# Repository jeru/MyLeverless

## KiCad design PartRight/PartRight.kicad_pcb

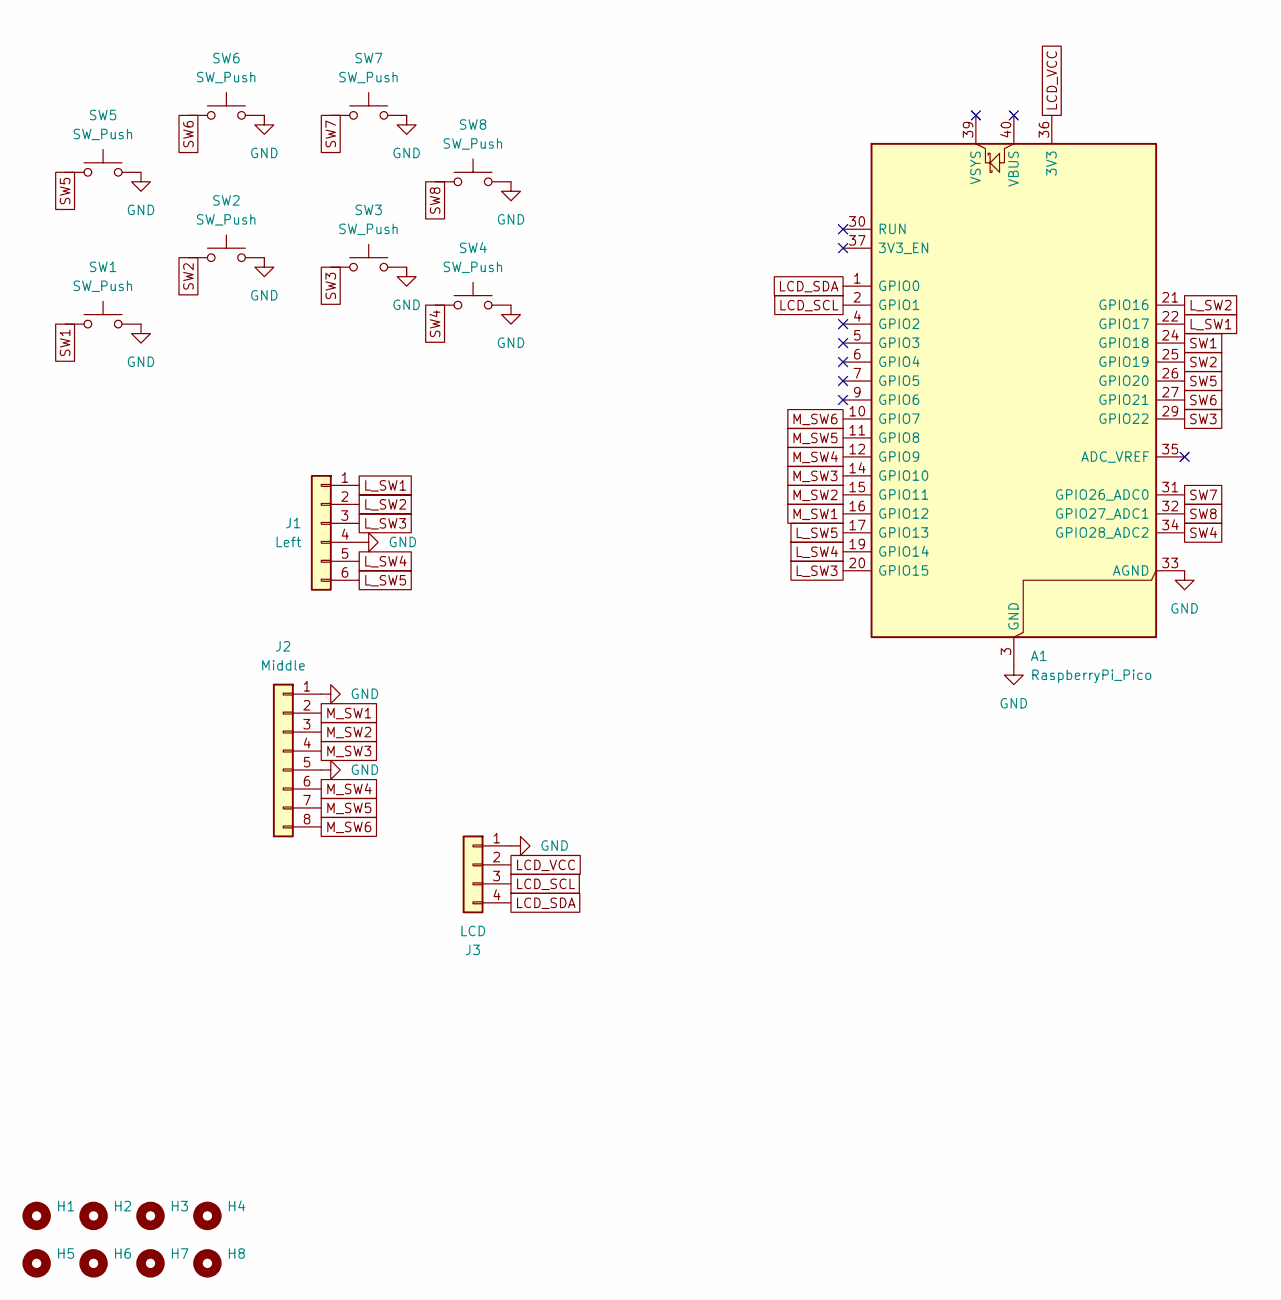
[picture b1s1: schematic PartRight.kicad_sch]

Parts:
A1: RaspberryPi_Pico; RaspberryPi_Pico_Common_SMD
H1, H2, H3, H4, H5, H6, H7, H8: MountingHole; MountingHole_3.2mm_M3_DIN965
J1: Left; PinHeader_1x06_P2.54mm_Horizontal
J2: Middle; PinHeader_1x08_P2.54mm_Horizontal
J3: LCD; PinHeader_1x04_P2.54mm_Horizontal
SW1, SW2, SW3, SW4, SW5, SW6, SW7, SW8: SW_Push; SW_MX_HotSwap_PTH

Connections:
GND: A1.3 (GND), A1.8 (GND), A1.13 (GND), A1.18 (GND), A1.23 (GND), A1.28 (GND), A1.33 (AGND), A1.38 (GND), J1.4, J2.1, J2.5, J3.1, SW1.2, SW2.2, SW3.2, SW4.2, SW5.2, SW6.2, SW7.2, SW8.2
LCD_SCL: A1.2 (GPIO1), J3.3
LCD_SDA: A1.1 (GPIO0), J3.4
LCD_VCC: A1.36 (3V3), J3.2
L_SW1: A1.22 (GPIO17), J1.1
L_SW2: A1.21 (GPIO16), J1.2
L_SW3: A1.20 (GPIO15), J1.3
L_SW4: A1.19 (GPIO14), J1.5
L_SW5: A1.17 (GPIO13), J1.6
M_SW1: A1.16 (GPIO12), J2.2
M_SW2: A1.15 (GPIO11), J2.3
M_SW3: A1.14 (GPIO10), J2.4
M_SW4: A1.12 (GPIO9), J2.6
M_SW5: A1.11 (GPIO8), J2.7
M_SW6: A1.10 (GPIO7), J2.8
SW1: A1.24 (GPIO18), SW1.1
SW2: A1.25 (GPIO19), SW2.1
SW3: A1.29 (GPIO22), SW3.1
SW4: A1.34 (GPIO28_ADC2), SW4.1
SW5: A1.26 (GPIO20), SW5.1
SW6: A1.27 (GPIO21), SW6.1
SW7: A1.31 (GPIO26_ADC0), SW7.1
SW8: A1.32 (GPIO27_ADC1), SW8.1

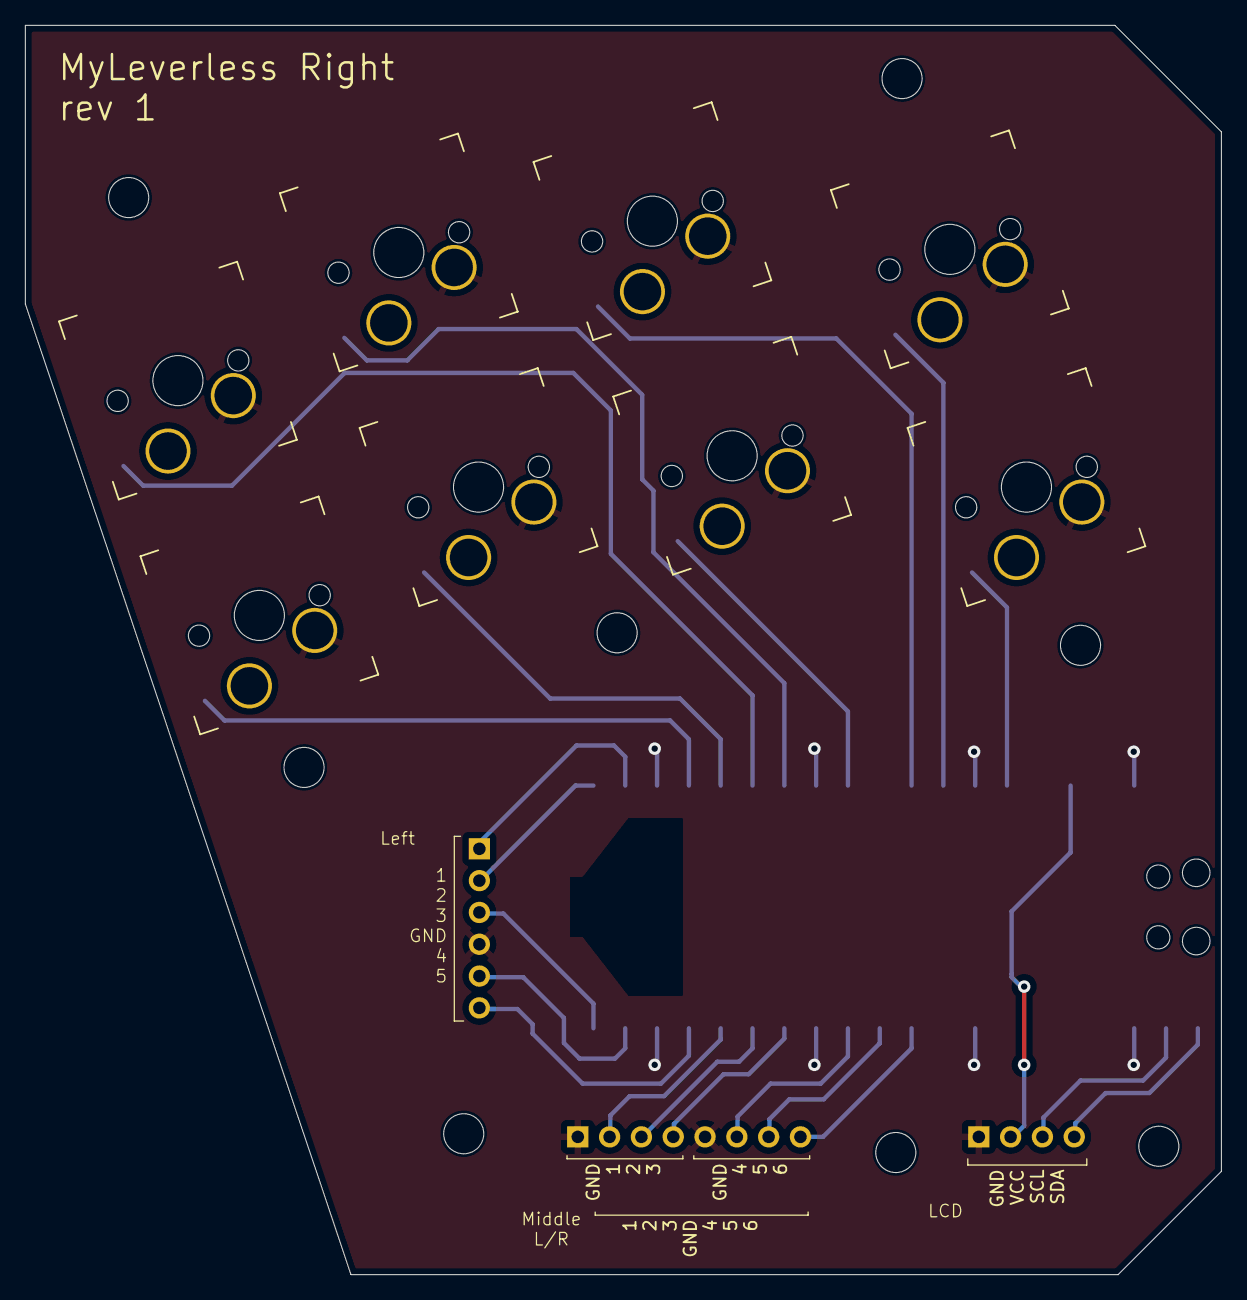
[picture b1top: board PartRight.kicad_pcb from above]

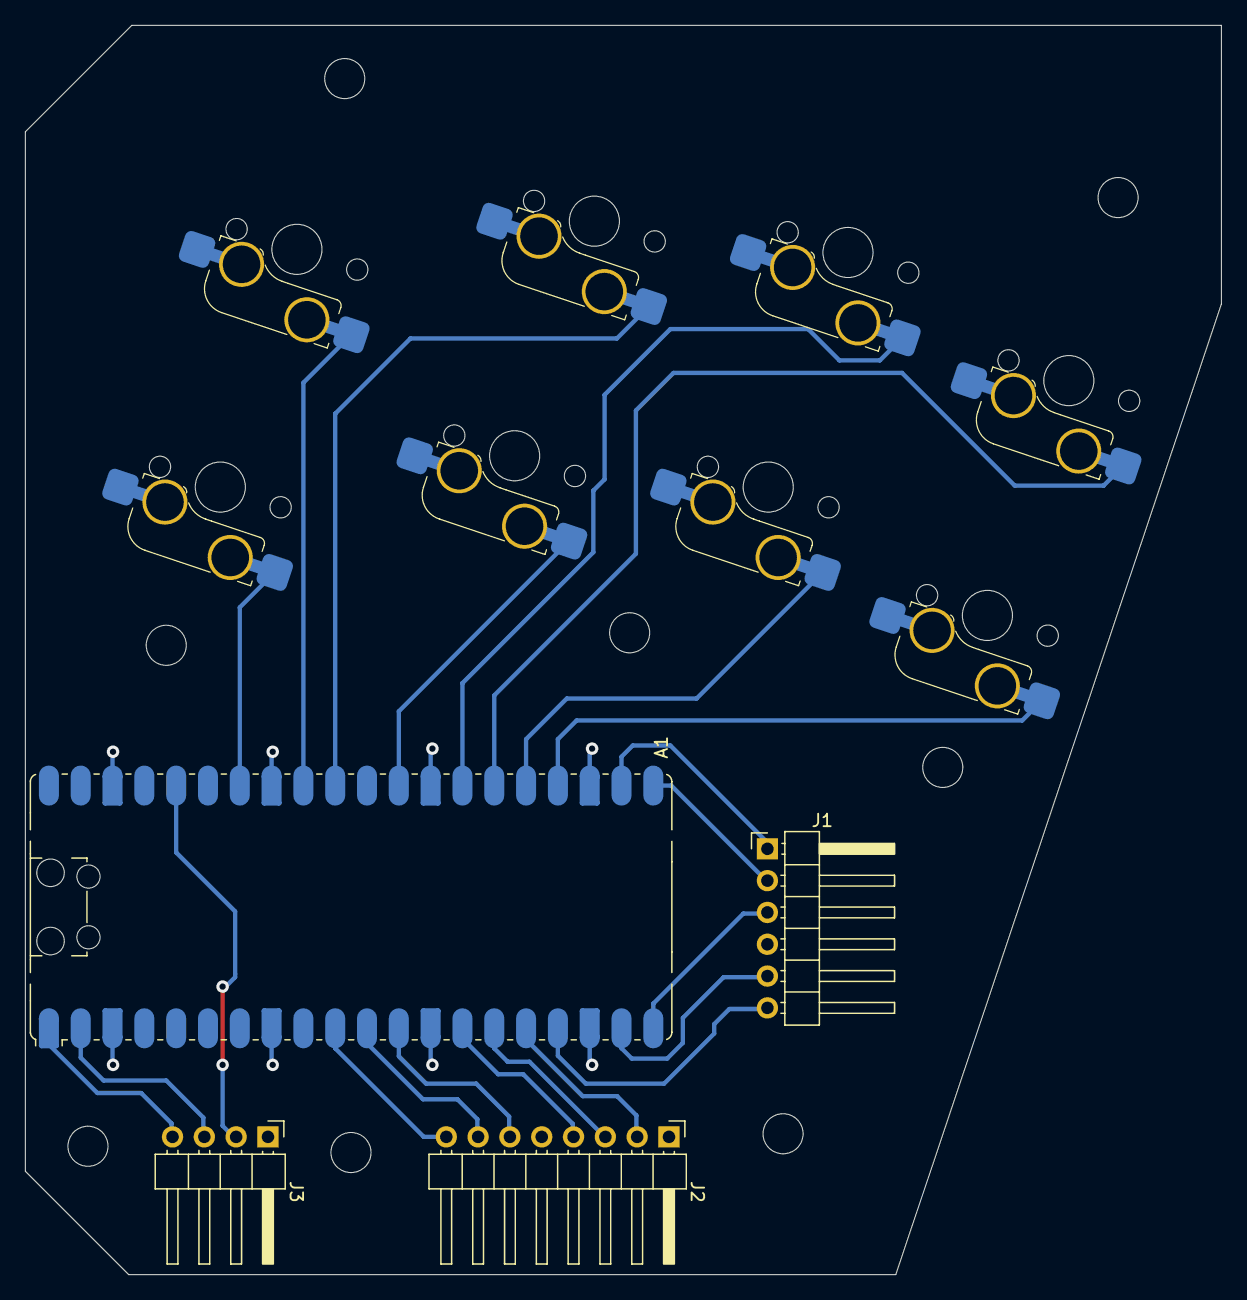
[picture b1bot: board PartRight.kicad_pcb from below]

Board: 2 copper layers, 95.5 x 99.8 mm, 20 parts (4 on the bottom side), 23 nets.

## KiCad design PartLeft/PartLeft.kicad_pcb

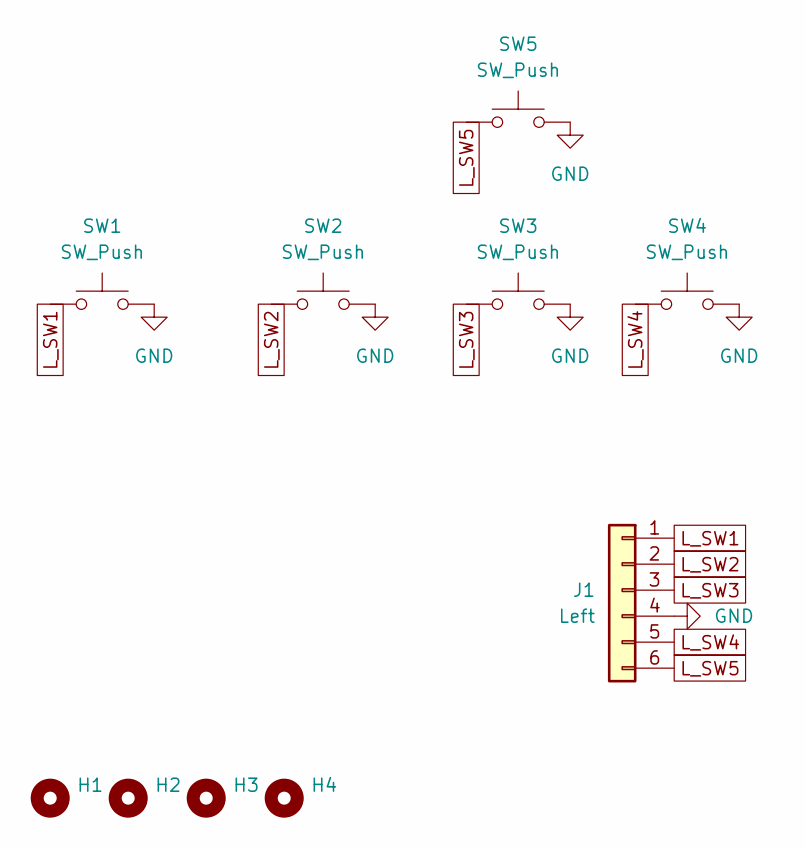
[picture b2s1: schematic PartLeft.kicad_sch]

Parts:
H1, H2, H3, H4: MountingHole; MountingHole_3.2mm_M3_DIN965
J1: Left; PinHeader_1x06_P2.54mm_Horizontal
SW1, SW2, SW3, SW4, SW5: SW_Push; SW_MX_HotSwap_PTH

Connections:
GND: J1.4, SW1.2, SW2.2, SW3.2, SW4.2, SW5.2
L_SW1: J1.1, SW1.1
L_SW2: J1.2, SW2.1
L_SW3: J1.3, SW3.1
L_SW4: J1.5, SW4.1
L_SW5: J1.6, SW5.1

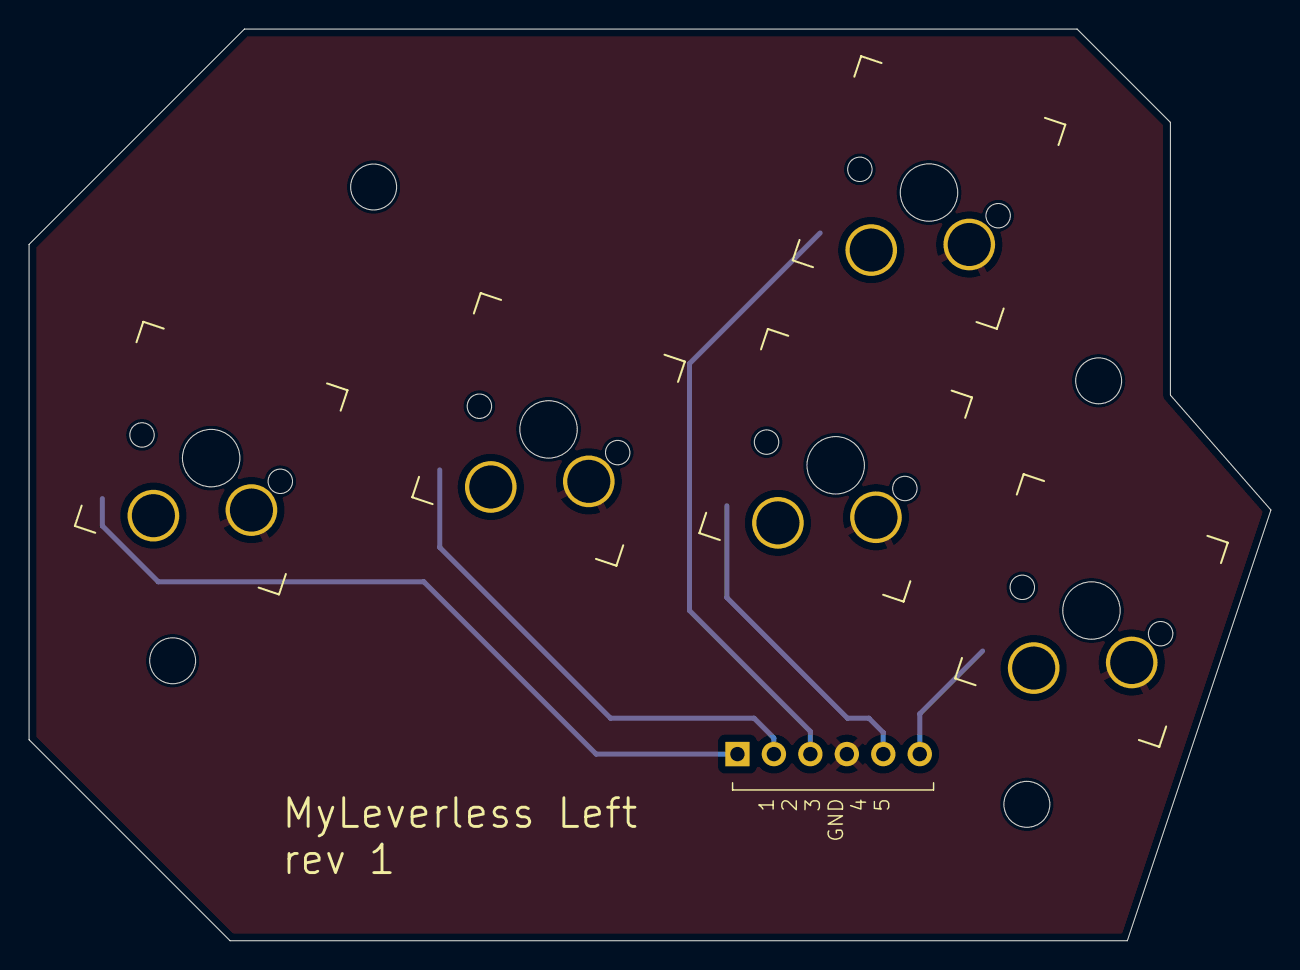
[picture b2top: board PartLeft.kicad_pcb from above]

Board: 2 copper layers, 86.5 x 63.5 mm, 10 parts (1 on the bottom side), 6 nets.

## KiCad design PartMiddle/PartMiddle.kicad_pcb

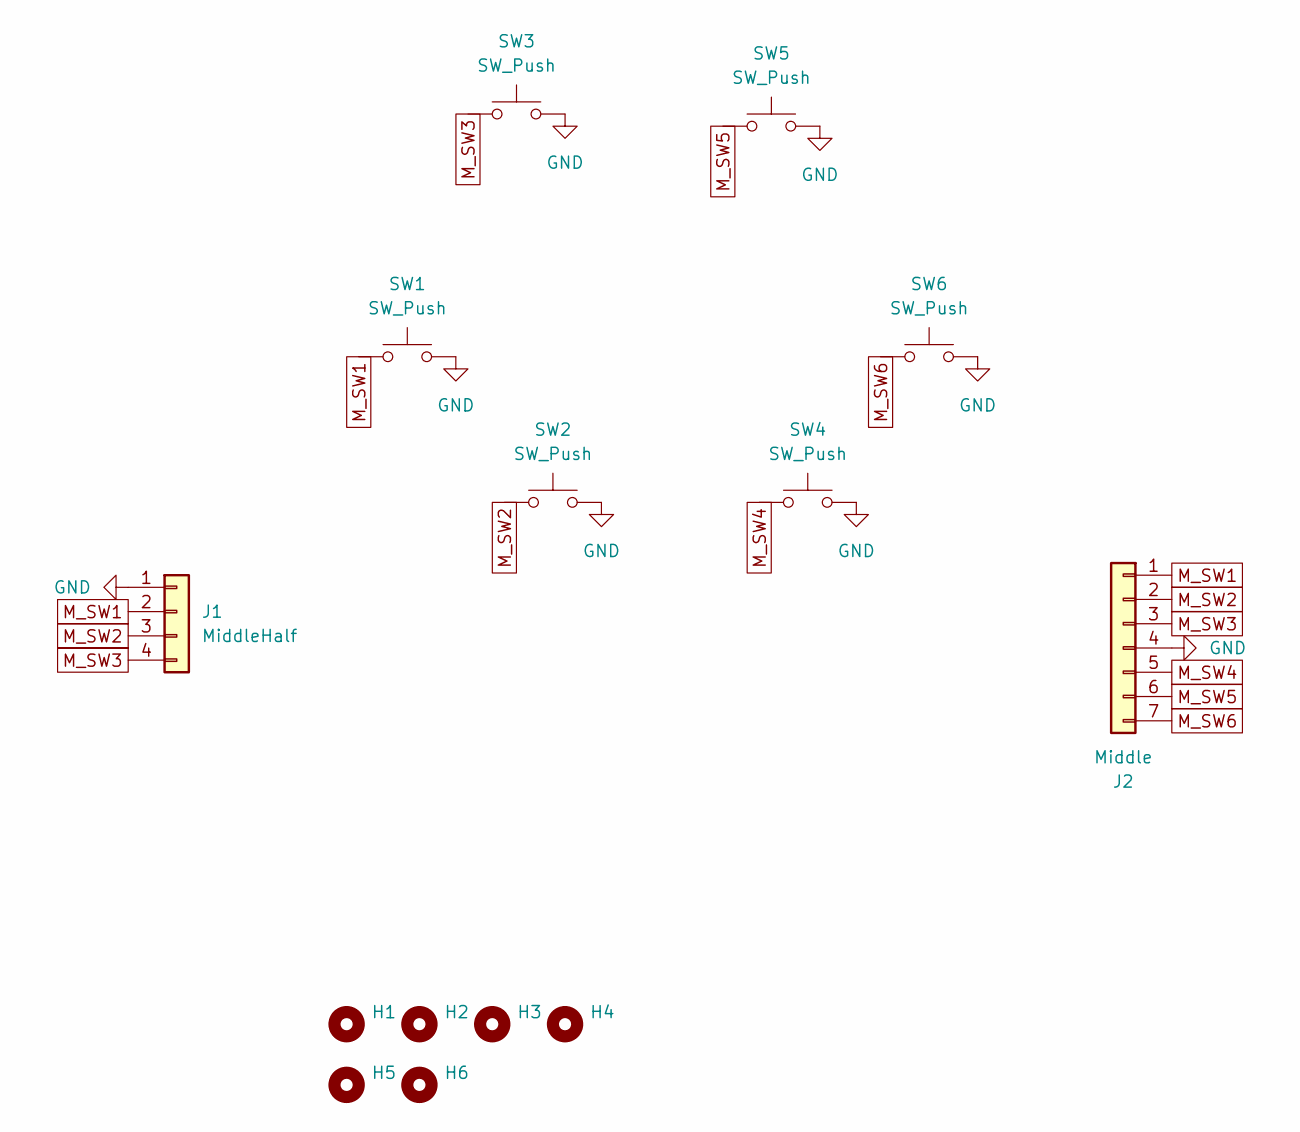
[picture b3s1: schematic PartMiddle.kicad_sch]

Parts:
H1, H2, H3, H4, H5, H6: MountingHole; MountingHole_3.2mm_M3_DIN965
J1: MiddleHalf; PinHeader_1x04_P2.54mm_Horizontal
J2: Middle; PinHeader_1x07_P2.54mm_Horizontal
SW1, SW2, SW3, SW4, SW5, SW6: SW_Push; SW_MX_HotSwap_PTH

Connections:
GND: J1.1, J2.4, SW1.2, SW2.2, SW3.2, SW4.2, SW5.2, SW6.2
M_SW1: J1.2, J2.1, SW1.1
M_SW2: J1.3, J2.2, SW2.1
M_SW3: J1.4, J2.3, SW3.1
M_SW4: J2.5, SW4.1
M_SW5: J2.6, SW5.1
M_SW6: J2.7, SW6.1

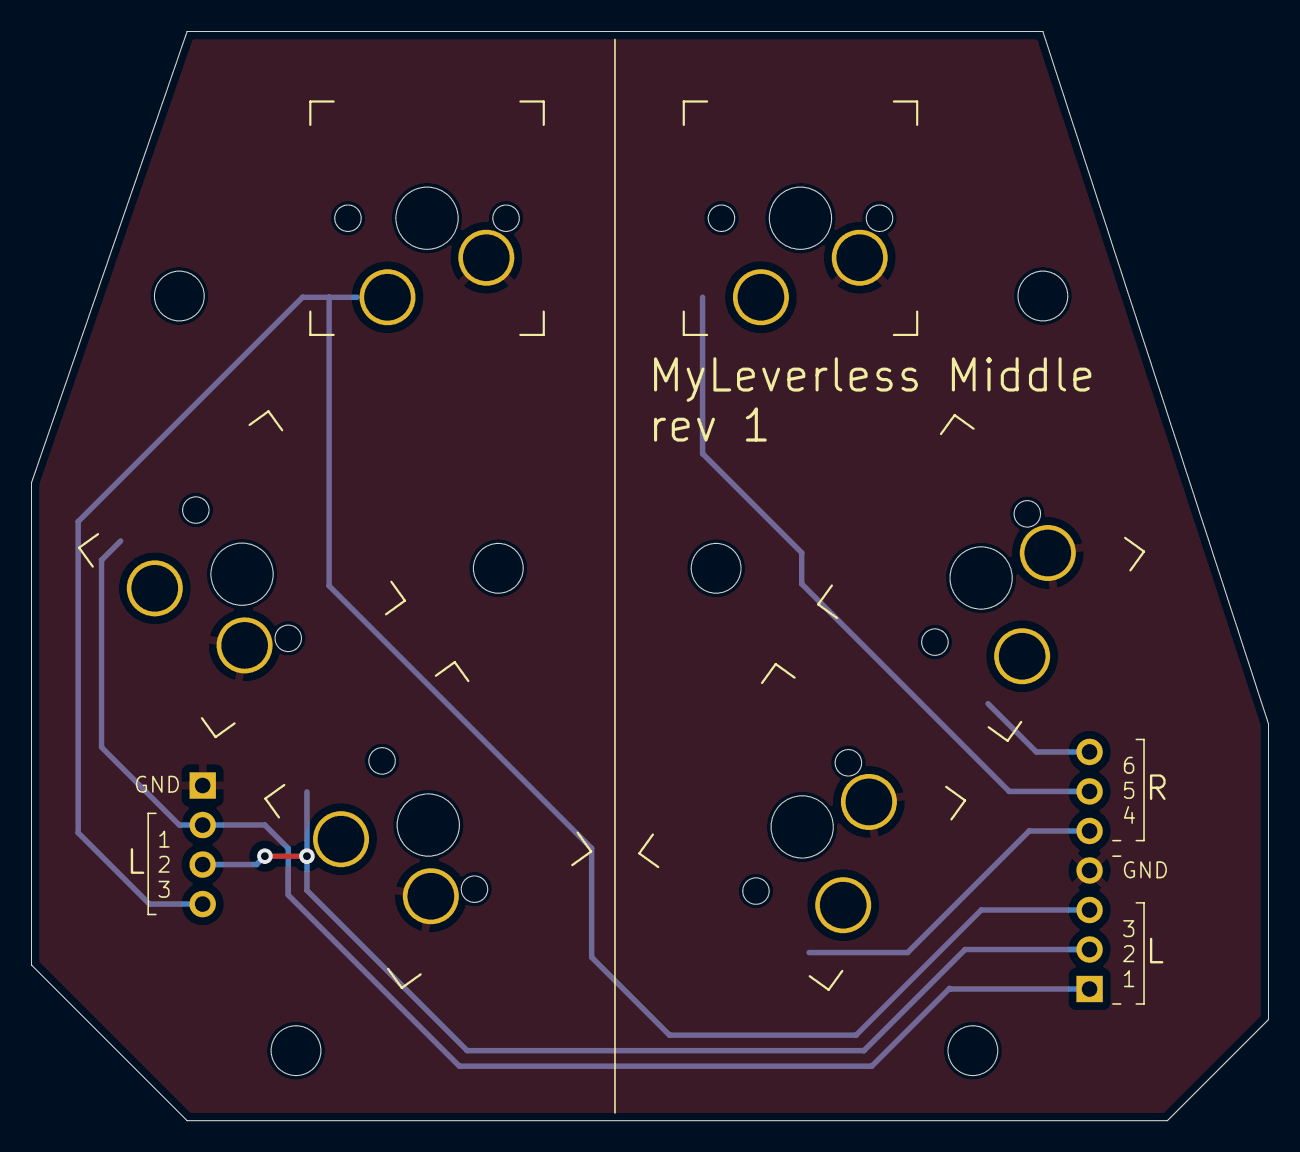
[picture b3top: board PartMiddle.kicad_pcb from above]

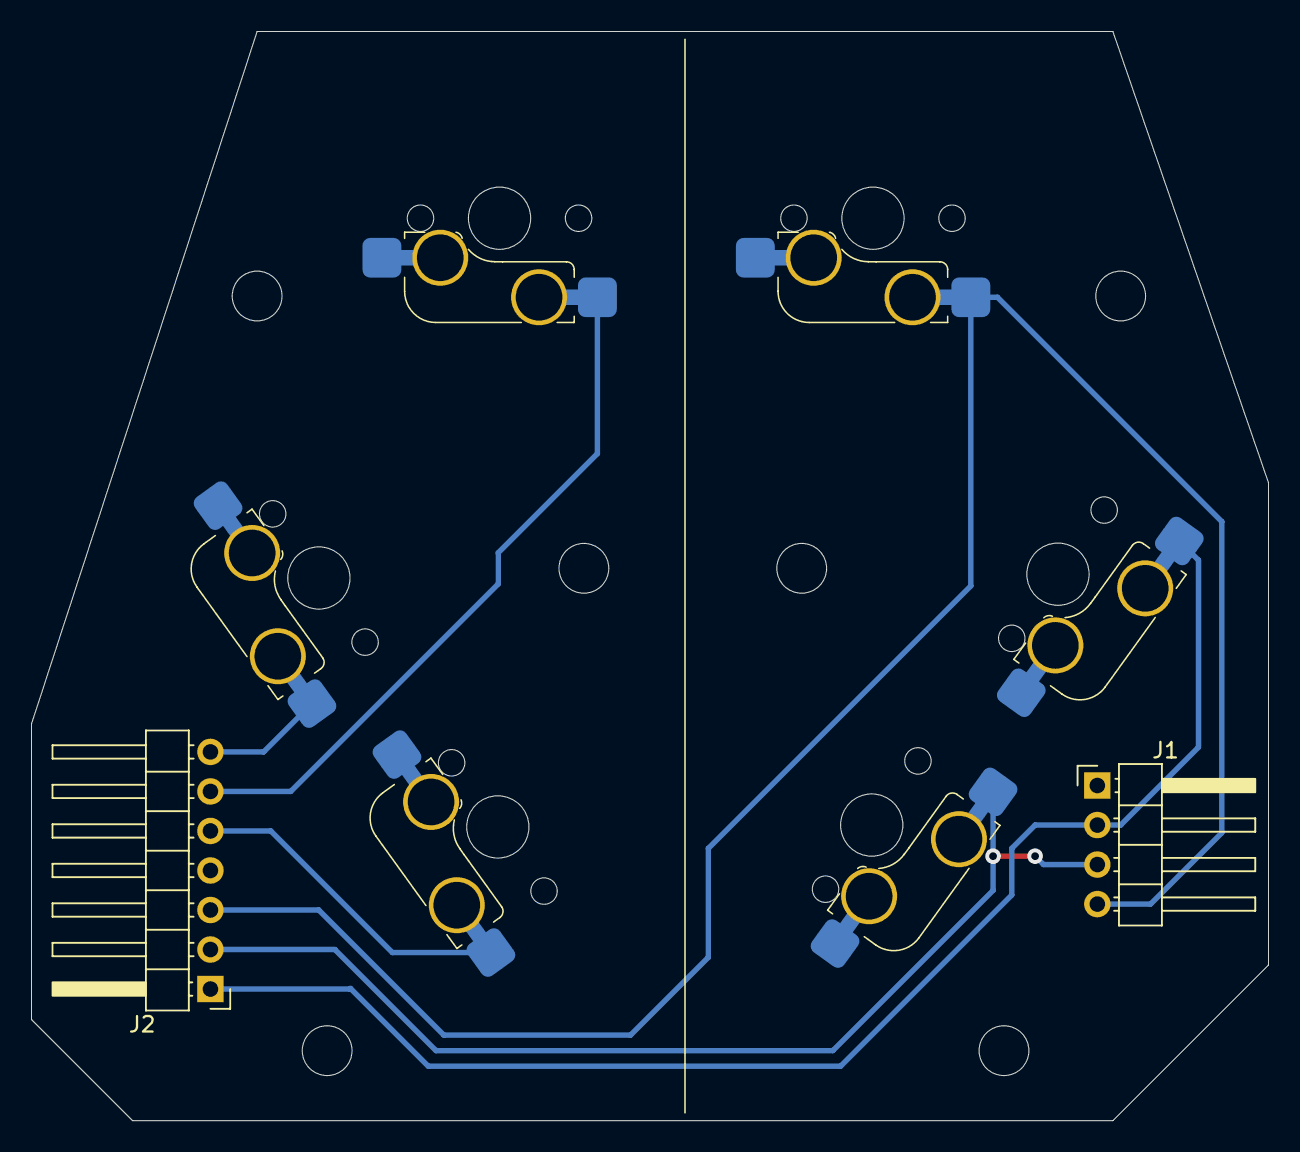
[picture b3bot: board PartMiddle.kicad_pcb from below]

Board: 2 copper layers, 79.5 x 70.0 mm, 14 parts (2 on the bottom side), 7 nets.

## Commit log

2025-05-08 Init commit.
2025-05-08 Import as submodule: https://github.com/siderakb/key-switches.pretty.git
2025-05-09 PCB for the middle part.
2025-05-09 PCB for the left part.
2025-05-09 PCB for the right part.
2025-05-09 Realign middle part pings to the right part.
2025-05-09 Ignore some kicad temporary files.
2025-05-09 PCB Left: larger name.
2025-05-09 Fix some rule checks.
2025-05-09 Ignore gerber files.
2025-05-09 Gerber configs of boards.
2025-05-09 Add license file.
2025-05-10 Upload the layout file.
    Created via LibreCAD.
2025-05-23 Outer lines for the layout file.
